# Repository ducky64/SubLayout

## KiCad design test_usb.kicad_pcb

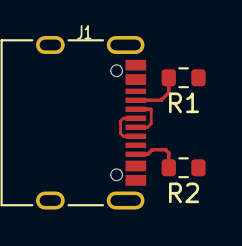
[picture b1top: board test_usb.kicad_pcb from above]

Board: 2 copper layers, 3 parts (0 on the bottom side), 6 nets.

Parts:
J1: COM-15111; USB_C_Receptacle_XKB_U262-16XN-4BVC11
R1, R2: ±1% 1/10W Thick Film Resistors 75V ±100ppm/? -55?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; R_0603_1608Metric

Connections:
usb.conn.cc.cc1: J1.A5, R1.2
usb.conn.cc.cc2: J1.B5, R2.2
usb.gnd: J1.A1, J1.A12, J1.B1, J1.B12, J1.S1, R1.1, R2.1
usb.pwr: J1.A4, J1.A9, J1.B4, J1.B9
usb.usb.dm: J1.A7, J1.B7
usb.usb.dp: J1.A6, J1.B6

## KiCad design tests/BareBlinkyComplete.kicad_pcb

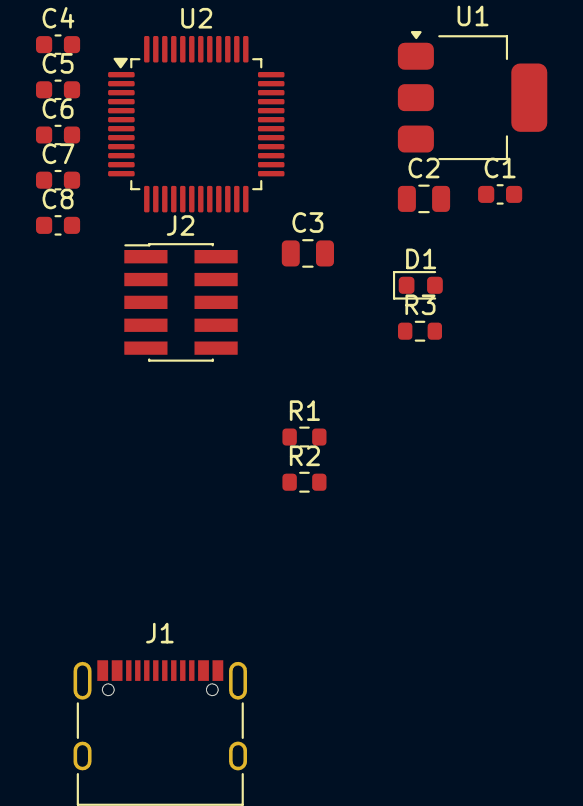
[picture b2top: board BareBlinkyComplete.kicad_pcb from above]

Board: 2 copper layers, 16 parts (0 on the bottom side), 12 nets, no tracks yet.

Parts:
C1, C4, C5, C6: 50V 100nF X7R ±10% 0603 Multilayer Ceramic Capaci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; C_0603_1608Metric
C2: X5R 25V ±10% 10uF 0805 Multilayer Ceramic Capacit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; C_0805_2012Metric
C3: 25V 4.7uF X5R ±10% 0805 Multilayer Ceramic Capaci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; C_0805_2012Metric
C7: 50V 10nF X7R ±10% 0603 Multilayer Ceramic Capacit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; C_0603_1608Metric
C8: 50V 1uF X5R ±10% 0603 Multilayer Ceramic Capacito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; C_0603_1608Metric
D1: Red 615~630nm 1.9~2.2V 0603 Light Emitting Diodes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; LED_0603_1608Metric
J1: COM-15111; USB_C_Receptacle_XKB_U262-16XN-4BVC11
J2: PinHeader1.27 Shrouded 2x5; PinHeader_2x05_P1.27mm_Vertical_SMD
R1, R2, R3: ±1% 1/10W Thick Film Resistors 75V ±100ppm/? -55?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; R_0603_1608Metric
U1: LD1117S33TR; SOT-223-3_TabPin2
U2: STM32F103xxT6; LQFP-48_7x7mm_P0.5mm

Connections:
led.res.a: D1.1, R3.1
led.signal: D1.2, U2.10
mcu.reset_node: J2.10, U2.7
mcu.swd_node.swclk: J2.4, U2.37
mcu.swd_node.swdio: J2.2, U2.34
reg.pwr_out: C2.1, C3.1, C4.1, C5.1, C6.1, C7.1, C8.1, J2.1, U1.2, U2.1, U2.9, U2.24, U2.36, U2.48
usb.conn.cc.cc1: J1.A5, R1.2
usb.conn.cc.cc2: J1.B5, R2.2
usb.gnd: C1.2, C2.2, C3.2, C4.2, C5.2, C6.2, C7.2, C8.2, J1.A1, J1.A12, J1.B1, J1.B12, J1.S1, J2.3, J2.5, J2.9, R1.1, R2.1, R3.2, U1.1, U2.8, U2.23, U2.35, U2.44, U2.47
usb.pwr: C1.1, J1.A4, J1.A9, J1.B4, J1.B9, U1.3
usb.usb.dm: J1.A7, J1.B7
usb.usb.dp: J1.A6, J1.B6
